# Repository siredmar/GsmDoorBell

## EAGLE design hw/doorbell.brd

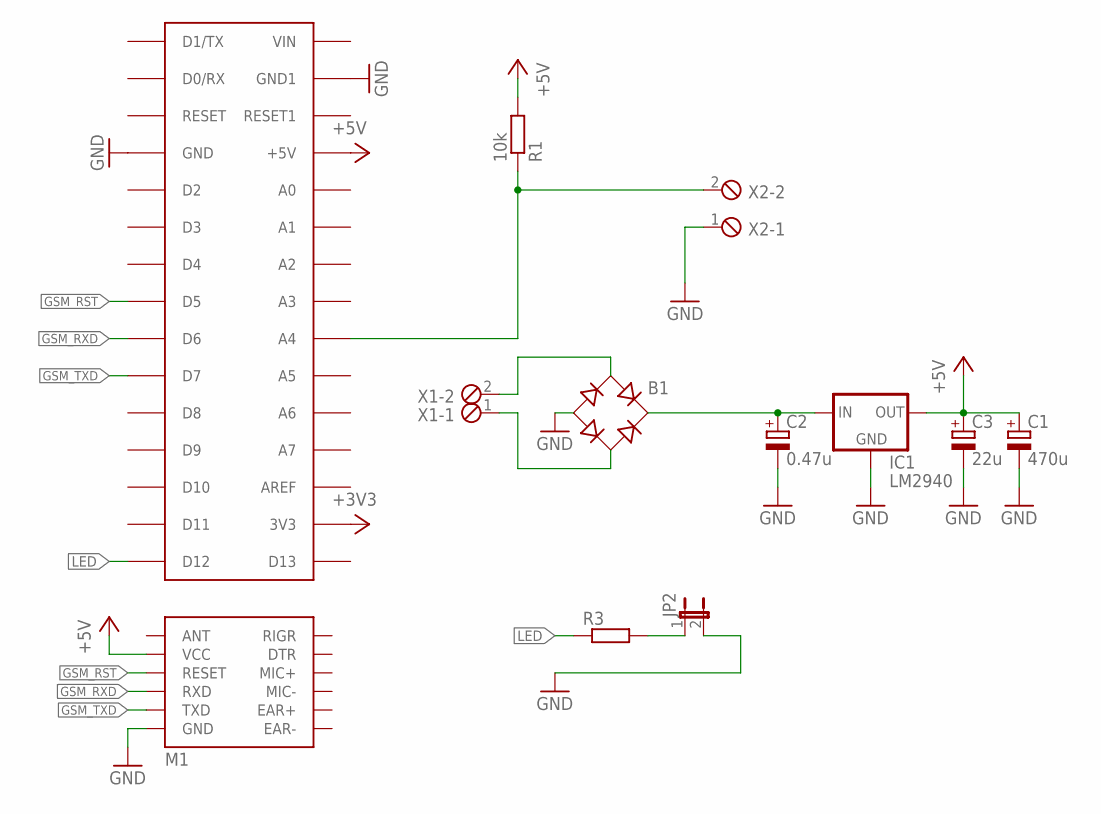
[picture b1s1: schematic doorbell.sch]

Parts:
B1: RB1A
C1: 470u; E2,5-6
C2: 0.47u; E2,5-5
C3: 22u; E2,5-5
IC1: LM2940; 78XXS
JP2: JP1E; JP1
M1: SIM800L
R1: 10k; 0207/10
R3: R-EU_0309/V; 0309V
U$1: ARDUINONANO; PDIP-32
X1, X2: MPT2; 2POL254

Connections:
+3V3: U$1.3V3
+5V: C1.+, C3.+, IC1.OUT, M1.VCC, R1.2, U$1.+5V
GND: B1.-, C1.-, C2.-, C3.-, IC1.GND, JP2.2, M1.GND, U$1.GND, U$1.GND1, X2.1
GSM_RST: M1.RESET, U$1.D5
GSM_RXD: M1.RXD, U$1.D6
GSM_TXD: M1.TXD, U$1.D7
INPUT: R1.1, U$1.A4, X2.2
LED: R3.1, U$1.D12
unnamed: B1.AC1, X1.2
unnamed: B1.AC2, X1.1
unnamed: B1.+, C2.+, IC1.IN
unnamed: JP2.1, R3.2

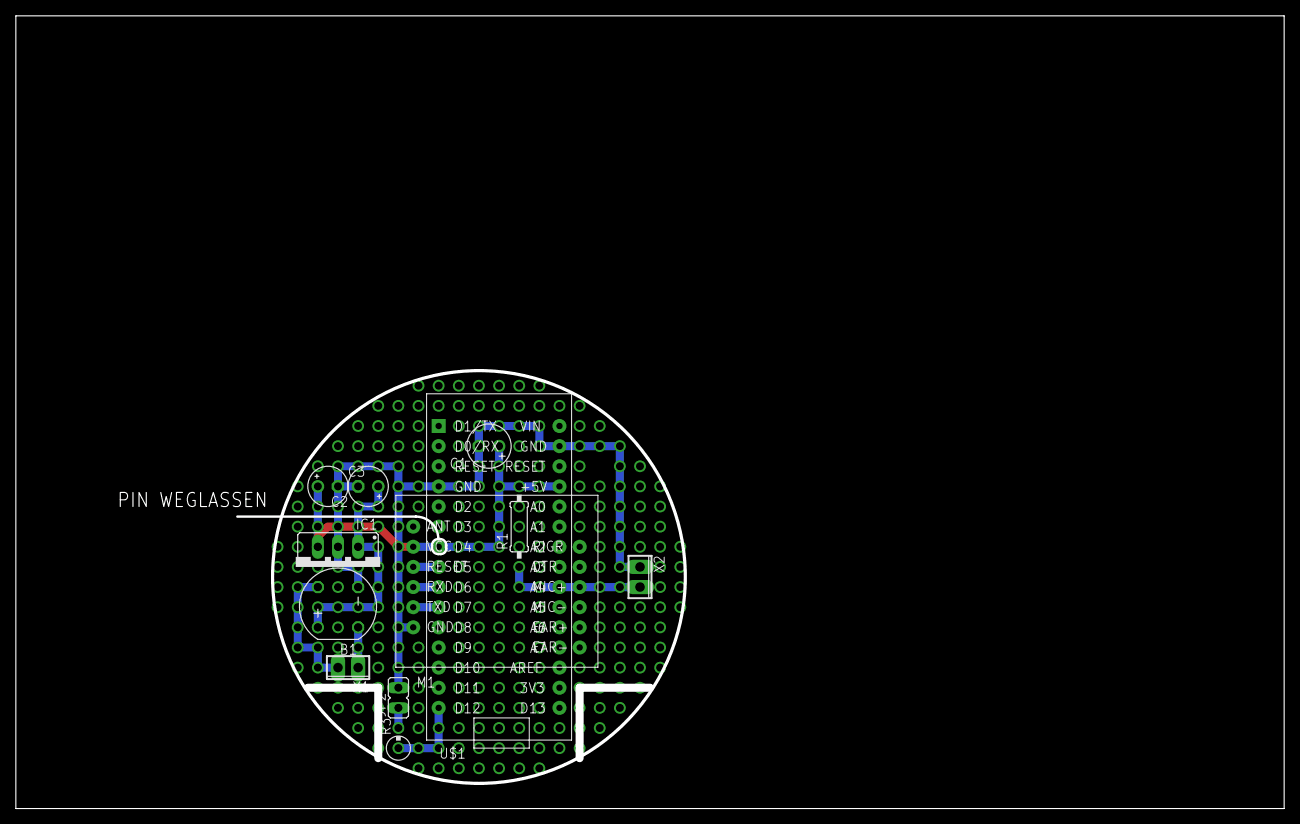
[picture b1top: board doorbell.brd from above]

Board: 2 copper layers, 160.0 x 100.0 mm, 12 parts (0 on the bottom side), 11 nets.

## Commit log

2018-09-22 Added SW and HW
2018-09-25 updated schematic and board
